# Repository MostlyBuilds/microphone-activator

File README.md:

This is a KiCad project for a microphone activator inspired by the Cloudlifter CL-1.

# Disclaimer
I do not have any affiliation with Cloud Microphones, the manufacturer of the
Cloudlifter CL-1. This project is being published for entertainment/educational
purposes.

- *Assumption of Risk:* Users acknowledge using the hardware project at their own risk.
- *No Warranty:* The Author (MostlyBuilds) provides the project "as-is" without any warranties.
- *Limitation of Liability:* The Author is not liable for any damages resulting from the use of this hardware project.

# Device Info
This device is a phantom powered microphone preamp, commonly called a microphone
activator. Devices like this are frequently used to boost quiet microphones
before the signal gets to an audio interface.

# Circuit Info
This circuit uses two LSK389C JFETs as a two-stage amplifier in what is referred
to as the [cascode](https://en.wikipedia.org/wiki/Cascode) configuration. All of
the components are of the SMT variety, with the resistors and capacitors in the
1206 package size.

For more details regarding the specific parts used, please refer to the YouTube
series. Each video in the series contains links in the description for parts
and tools that are relevant to the video.

# YouTube Video Series
This project was created as part of a YouTube video series that walks through
the teardown of a real CL-1, and the process of creating the circuit and a
custom PCB variant in KiCad.

The full project details and links to the videos can be found on the MostlyBuilds
website: [https://mostlybuilds.com/microphone-activator-series](https://mostlybuilds.com/microphone-activator-series/)

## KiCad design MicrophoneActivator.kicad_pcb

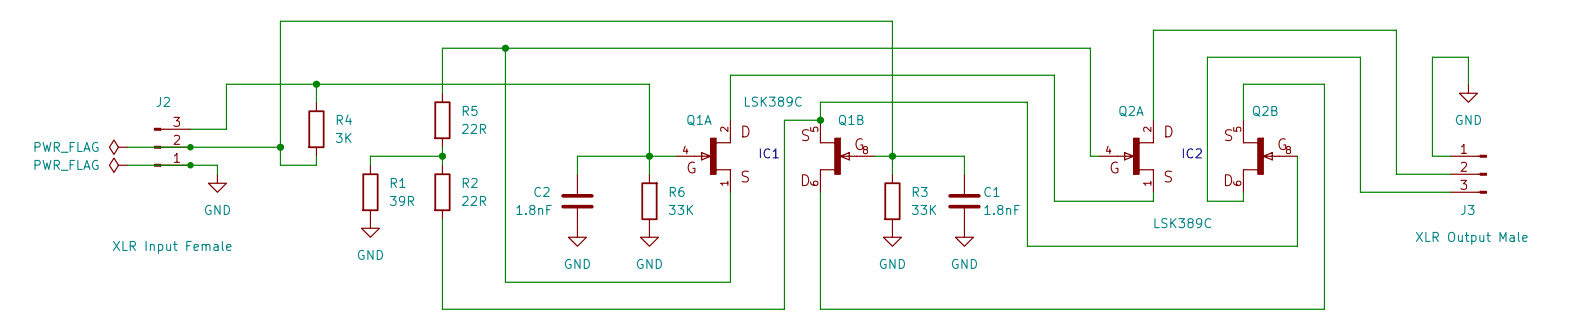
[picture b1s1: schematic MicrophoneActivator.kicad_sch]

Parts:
C1, C2: 1.8nF; C_1206_3216Metric
J2: XLR Input Female; PinHeader_1x03_P2.54mm_Vertical
J3: XLR Output Male; PinHeader_1x03_P2.54mm_Vertical
Q1, Q2: LSK389C; SO8
R1: 39R; R_1206_3216Metric
R2, R5: 22R; R_1206_3216Metric
R3: 33K; C_1206_3216Metric
R4: 3K; R_1206_3216Metric
R6: 33K; R_1206_3216Metric

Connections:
GND: C1.2, C2.1, J2.1, J3.1, R1.2, R3.2, R6.1
unnamed: C1.1, J2.2, Q1.8, R3.1, R4.2
unnamed: C2.2, J2.3, Q1.4, R4.1, R6.2
unnamed: J3.2, Q2.2
unnamed: J3.3, Q2.6
unnamed: Q1.1, Q2.4, R5.1
unnamed: Q1.2, Q2.1
unnamed: Q1.5, Q2.8, R2.2
unnamed: Q1.6, Q2.5
unnamed: R1.1, R2.1, R5.2

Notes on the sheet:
IC2
IC1

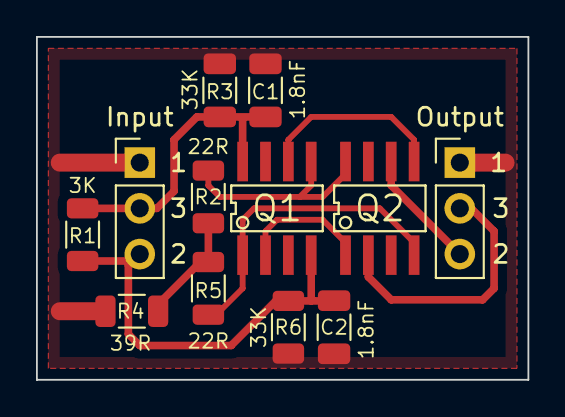
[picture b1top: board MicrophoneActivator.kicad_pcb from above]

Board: 2 copper layers, 27.3 x 19.0 mm, 12 parts (0 on the bottom side), 10 nets.
